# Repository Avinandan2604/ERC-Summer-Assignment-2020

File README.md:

# ERC-Summer-Assignment-2020

Here's the summer assignment 2020 ...
Done by Avinandan Nag
EAGLE Projects 
Circuit 1 for Q1 (PCB)
Circuit 2 for Q2 (PCB)
Circuits.pdf contains pdf that contains links for tinkercad circuits...
Some questions are done somewhat modified...
In arduino circuits
Q.2 instead of 3 digit 7 segment display i have used normal 16x2 LCD
Q.4 is somewhat incomplete ..
In digital and Analog Circuits
Q.2 instead  of counter from 0 to 99 i have done counter from 0 to 9
Extra question done from mechanical section (Chess bot isometric model)

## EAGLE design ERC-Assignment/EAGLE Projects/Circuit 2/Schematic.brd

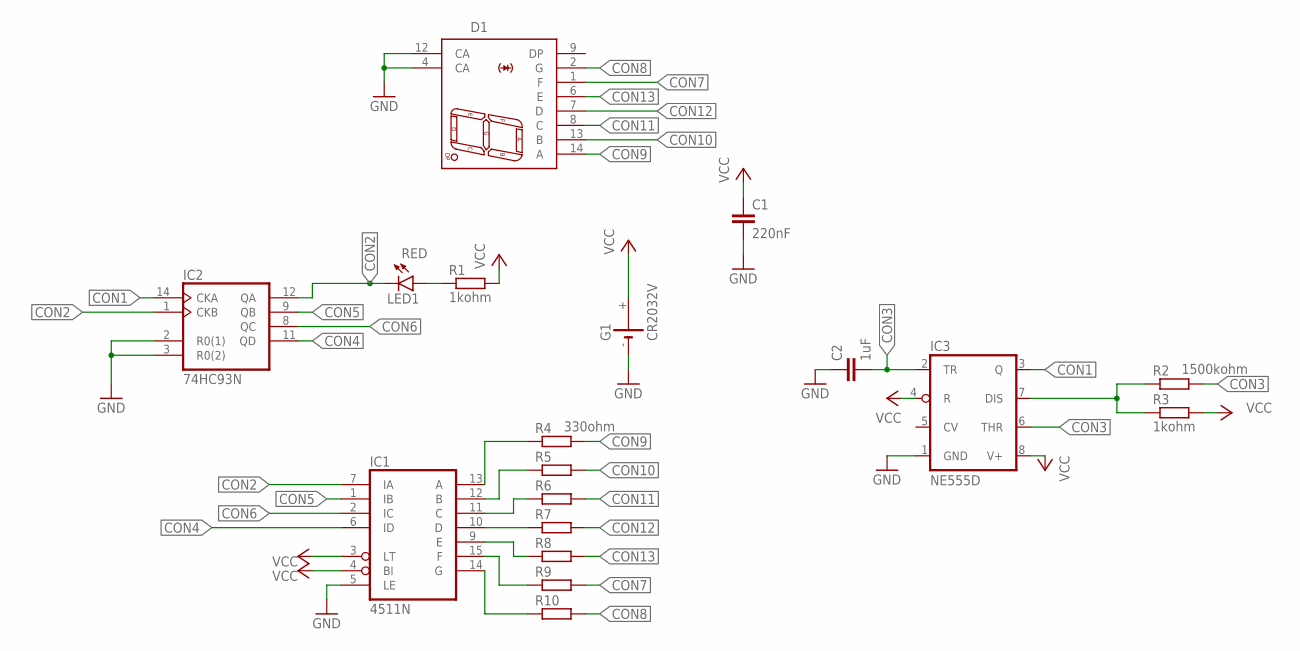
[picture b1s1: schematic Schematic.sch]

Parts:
C1: 220nF; C025-025X050
C2: 1uF; C025-025X050
D1: SA03; S*03
G1: CR2032V
IC1: 4511N; DIL16
IC2: 74HC93N; DIL14
IC3: NE555D; SO08
LED1: RED; LED3MM
R1, R3: 1kohm; 0204/7
R2: 1500kohm; 0204/7
R4: 330ohm; 0204/7
R5, R6, R7, R8, R9, R10: R-EU_0204/7; 0204/7

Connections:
CON1: IC2.14 (CKA), IC3.3 (Q)
CON2: IC1.7 (IA), IC2.1 (CKB), IC2.12 (QA), LED1.K (C)
CON3: C2.2, IC3.2 (TR), IC3.6 (THR), R2.2
CON4: IC1.6 (ID), IC2.11 (QD)
CON5: IC1.1 (IB), IC2.9 (QB)
CON6: IC1.2 (IC), IC2.8 (QC)
CON7: D1.1 (F), R9.2
CON8: D1.2 (G), R10.2
CON9: D1.14 (A), R4.2
CON10: D1.13 (B), R5.2
CON11: D1.8 (C), R6.2
CON12: D1.7 (D), R7.2
CON13: D1.6 (E), R8.2
GND: C1.2, C2.1, D1.4 (CA), D1.12 (CA), G1.-, IC1.5 (LE), IC2.2 (R0(1)), IC2.3 (R0(2)), IC2.10 (GND), IC3.1 (GND)
unnamed: LED1.A, R1.1
unnamed: IC3.7 (DIS), R2.1, R3.1
unnamed: IC1.13 (A), R4.1
unnamed: IC1.12 (B), R5.1
unnamed: IC1.11 (C), R6.1
unnamed: IC1.10 (D), R7.1
unnamed: IC1.9 (E), R8.1
unnamed: IC1.15 (F), R9.1
unnamed: IC1.14 (G), R10.1
VCC: C1.1, G1.+, IC1.3 (LT), IC1.4 (BI), IC2.5 (VCC), IC3.4 (R), IC3.8 (V+), R1.2, R3.2
VDD: IC1.16 (VDD)
VSS: IC1.8 (VSS)

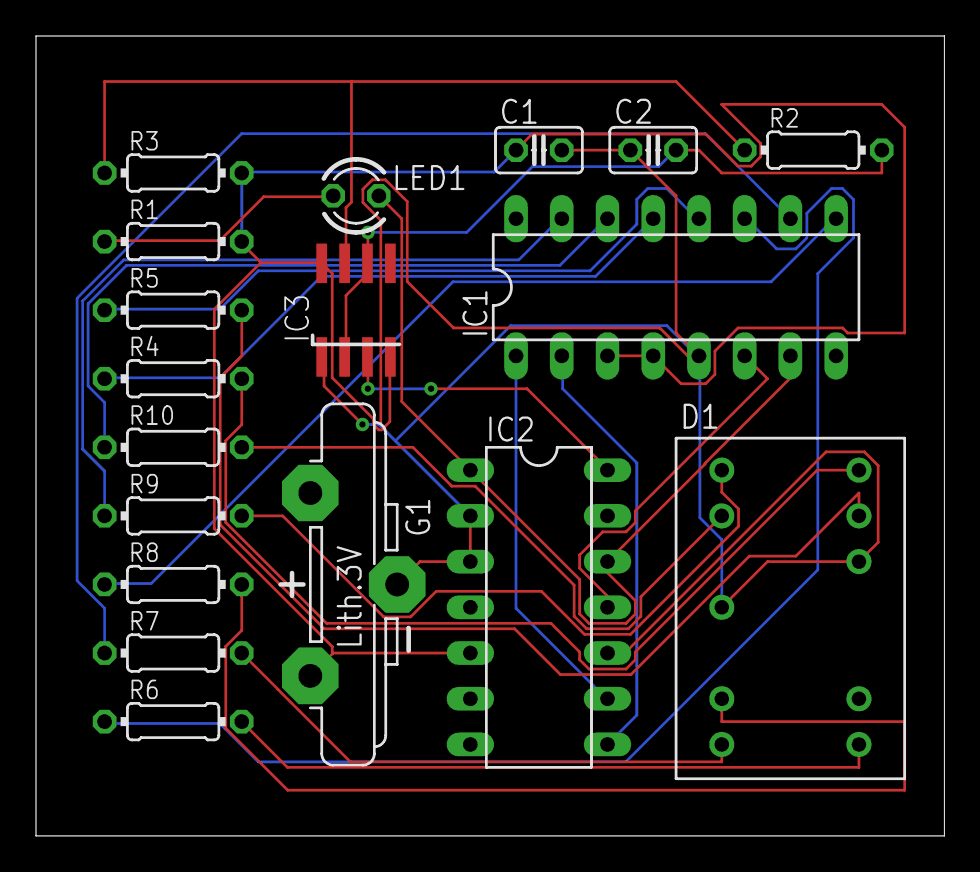
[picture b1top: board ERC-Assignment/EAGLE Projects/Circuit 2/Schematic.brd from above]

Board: 2 copper layers, 50.5 x 44.4 mm, 18 parts (0 on the bottom side), 24 nets.

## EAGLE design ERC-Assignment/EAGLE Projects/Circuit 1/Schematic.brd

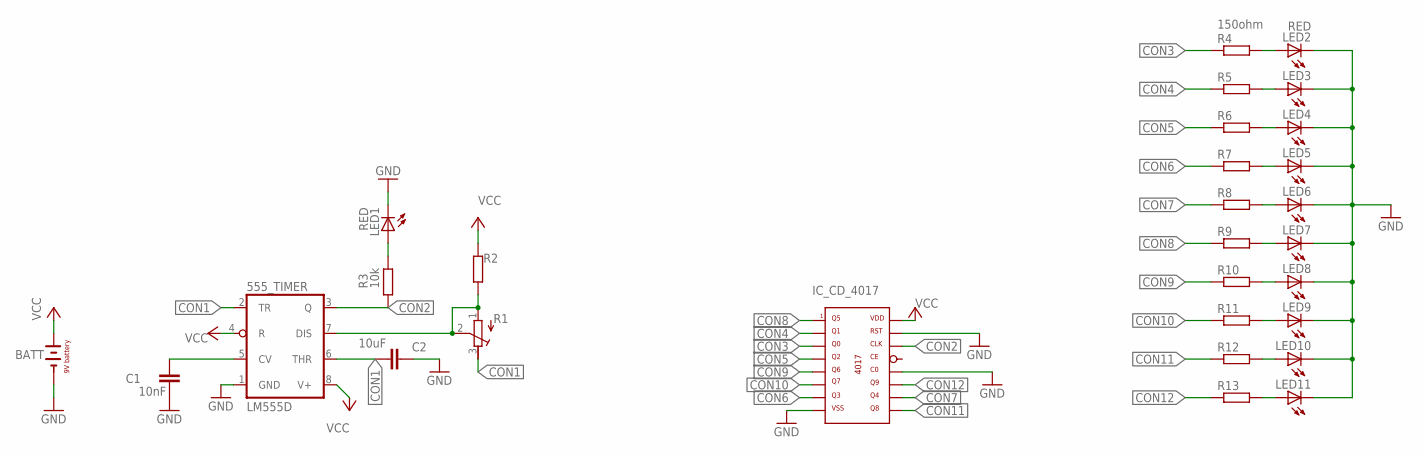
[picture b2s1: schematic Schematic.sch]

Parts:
555_TIMER: LM555D; SO08
BATT: -9VBAT; BAT
C1: 10nF; C025-025X050
C2: 10uF; C025-025X050
IC_CD_4017: -4017; DIL16
LED1, LED2: RED; LED3MM
LED3, LED4, LED5, LED6, LED7, LED8, LED9, LED10, LED11: LED3MM
R1: R-TRIMM64P; RTRIM64P
R2, R5, R6, R7, R8, R9, R10, R11, R12, R13: R-EU_0204/7; 0204/7
R3: 10k; 0204/7
R4: 150ohm; 0204/7

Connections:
CON1: 555_TIMER.2 (TR), 555_TIMER.6 (THR), C2.1, R1.3 (E)
CON2: 555_TIMER.3 (Q), IC_CD_4017.14 (CLK), R3.1
CON3: IC_CD_4017.3 (Q0), R4.1
CON4: IC_CD_4017.2 (Q1), R5.1
CON5: IC_CD_4017.4 (Q2), R6.1
CON6: IC_CD_4017.7 (Q3), R7.1
CON7: IC_CD_4017.10 (Q4), R8.1
CON8: IC_CD_4017.1 (Q5), R9.1
CON9: IC_CD_4017.5 (Q6), R10.1
CON10: IC_CD_4017.6 (Q7), R11.1
CON11: IC_CD_4017.9 (Q8), R12.1
CON12: IC_CD_4017.11 (Q9), R13.1
GND: 555_TIMER.1 (GND), BATT.-, C1.2, C2.2, IC_CD_4017.8 (VSS), IC_CD_4017.12 (C0), IC_CD_4017.15 (RST), LED1.A, LED1.K (C), LED2.K (C), LED3.K (C), LED4.K (C), LED5.K (C), LED6.K (C), LED7.K (C), LED8.K (C), LED9.K (C), LED10.K (C), LED11.K (C), R3.2
unnamed: 555_TIMER.5 (CV), C1.1
unnamed: 555_TIMER.7 (DIS), R1.1 (A), R1.2 (S), R2.1
unnamed: LED2.A, R4.2
unnamed: LED3.A, R5.2
unnamed: LED4.A, R6.2
unnamed: LED5.A, R7.2
unnamed: LED6.A, R8.2
unnamed: LED7.A, R9.2
unnamed: LED8.A, R10.2
unnamed: LED9.A, R11.2
unnamed: LED10.A, R12.2
unnamed: LED11.A, R13.2
VCC: 555_TIMER.4 (R), 555_TIMER.8 (V+), BATT.+, IC_CD_4017.16 (VDD), R2.2

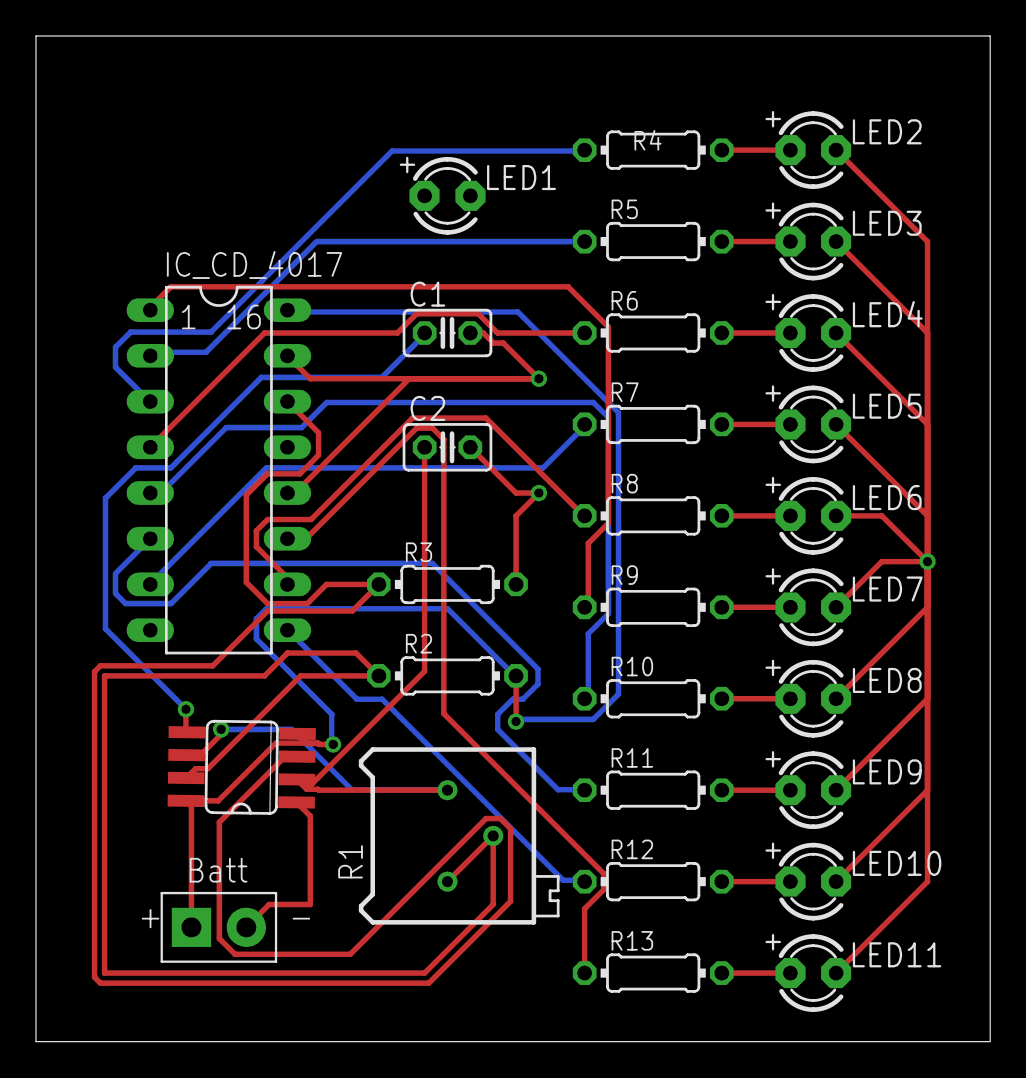
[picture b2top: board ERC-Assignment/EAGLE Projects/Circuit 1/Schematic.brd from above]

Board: 2 copper layers, 53.0 x 55.9 mm, 29 parts (0 on the bottom side), 26 nets.
